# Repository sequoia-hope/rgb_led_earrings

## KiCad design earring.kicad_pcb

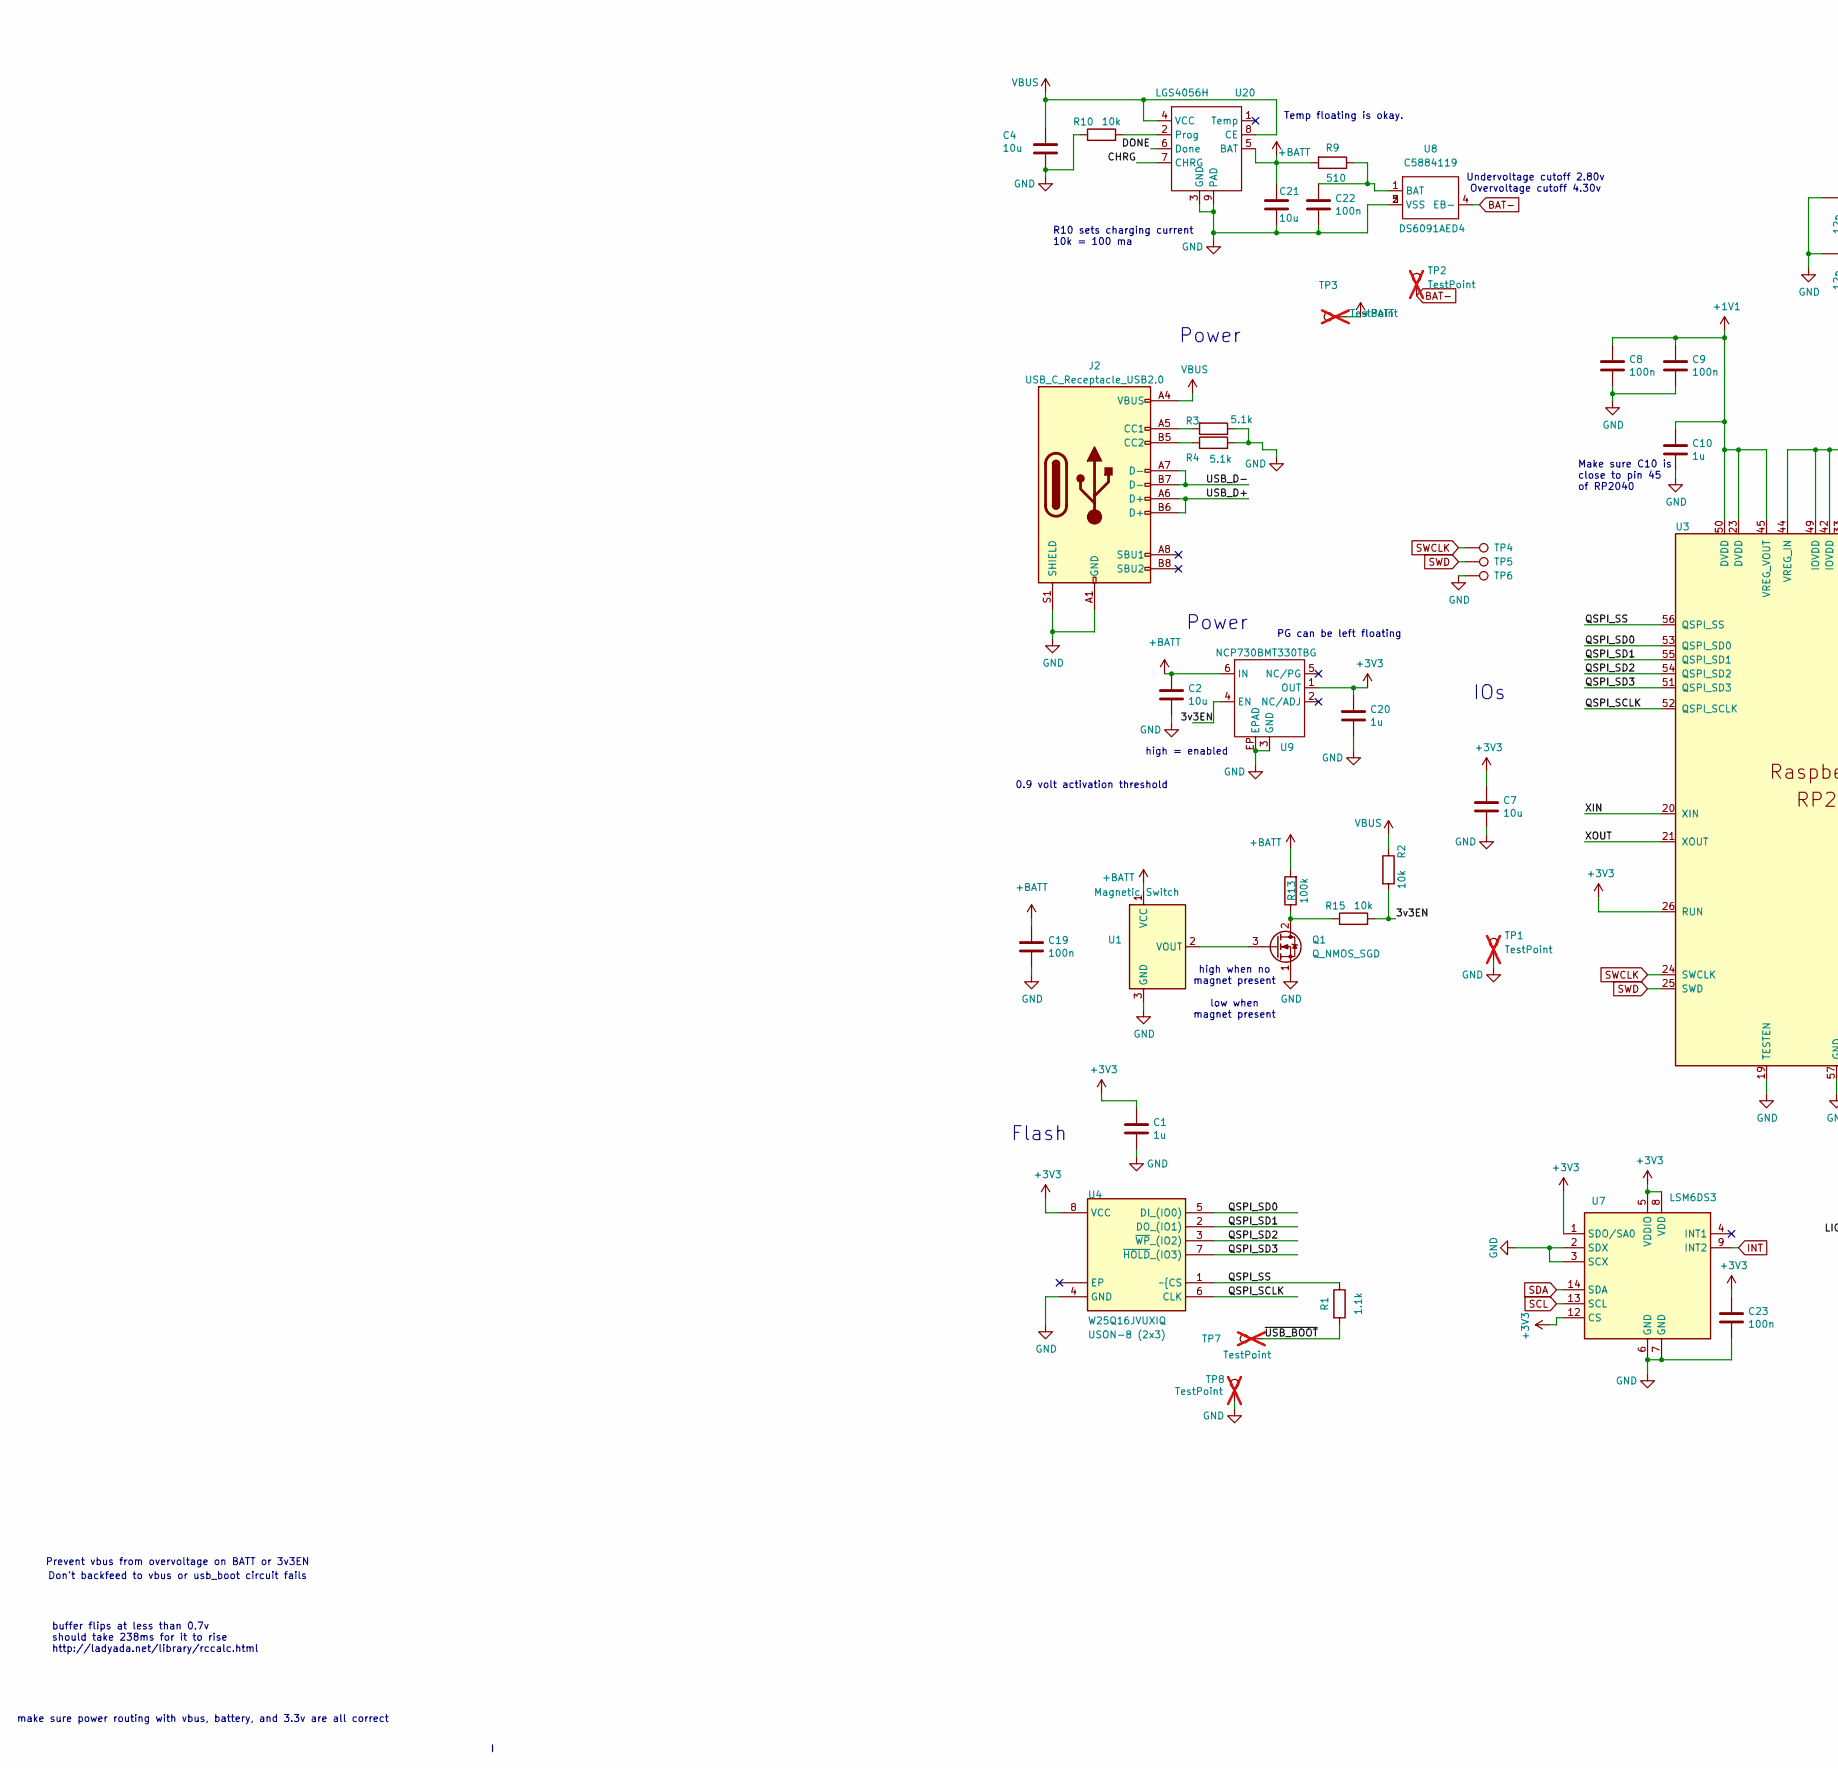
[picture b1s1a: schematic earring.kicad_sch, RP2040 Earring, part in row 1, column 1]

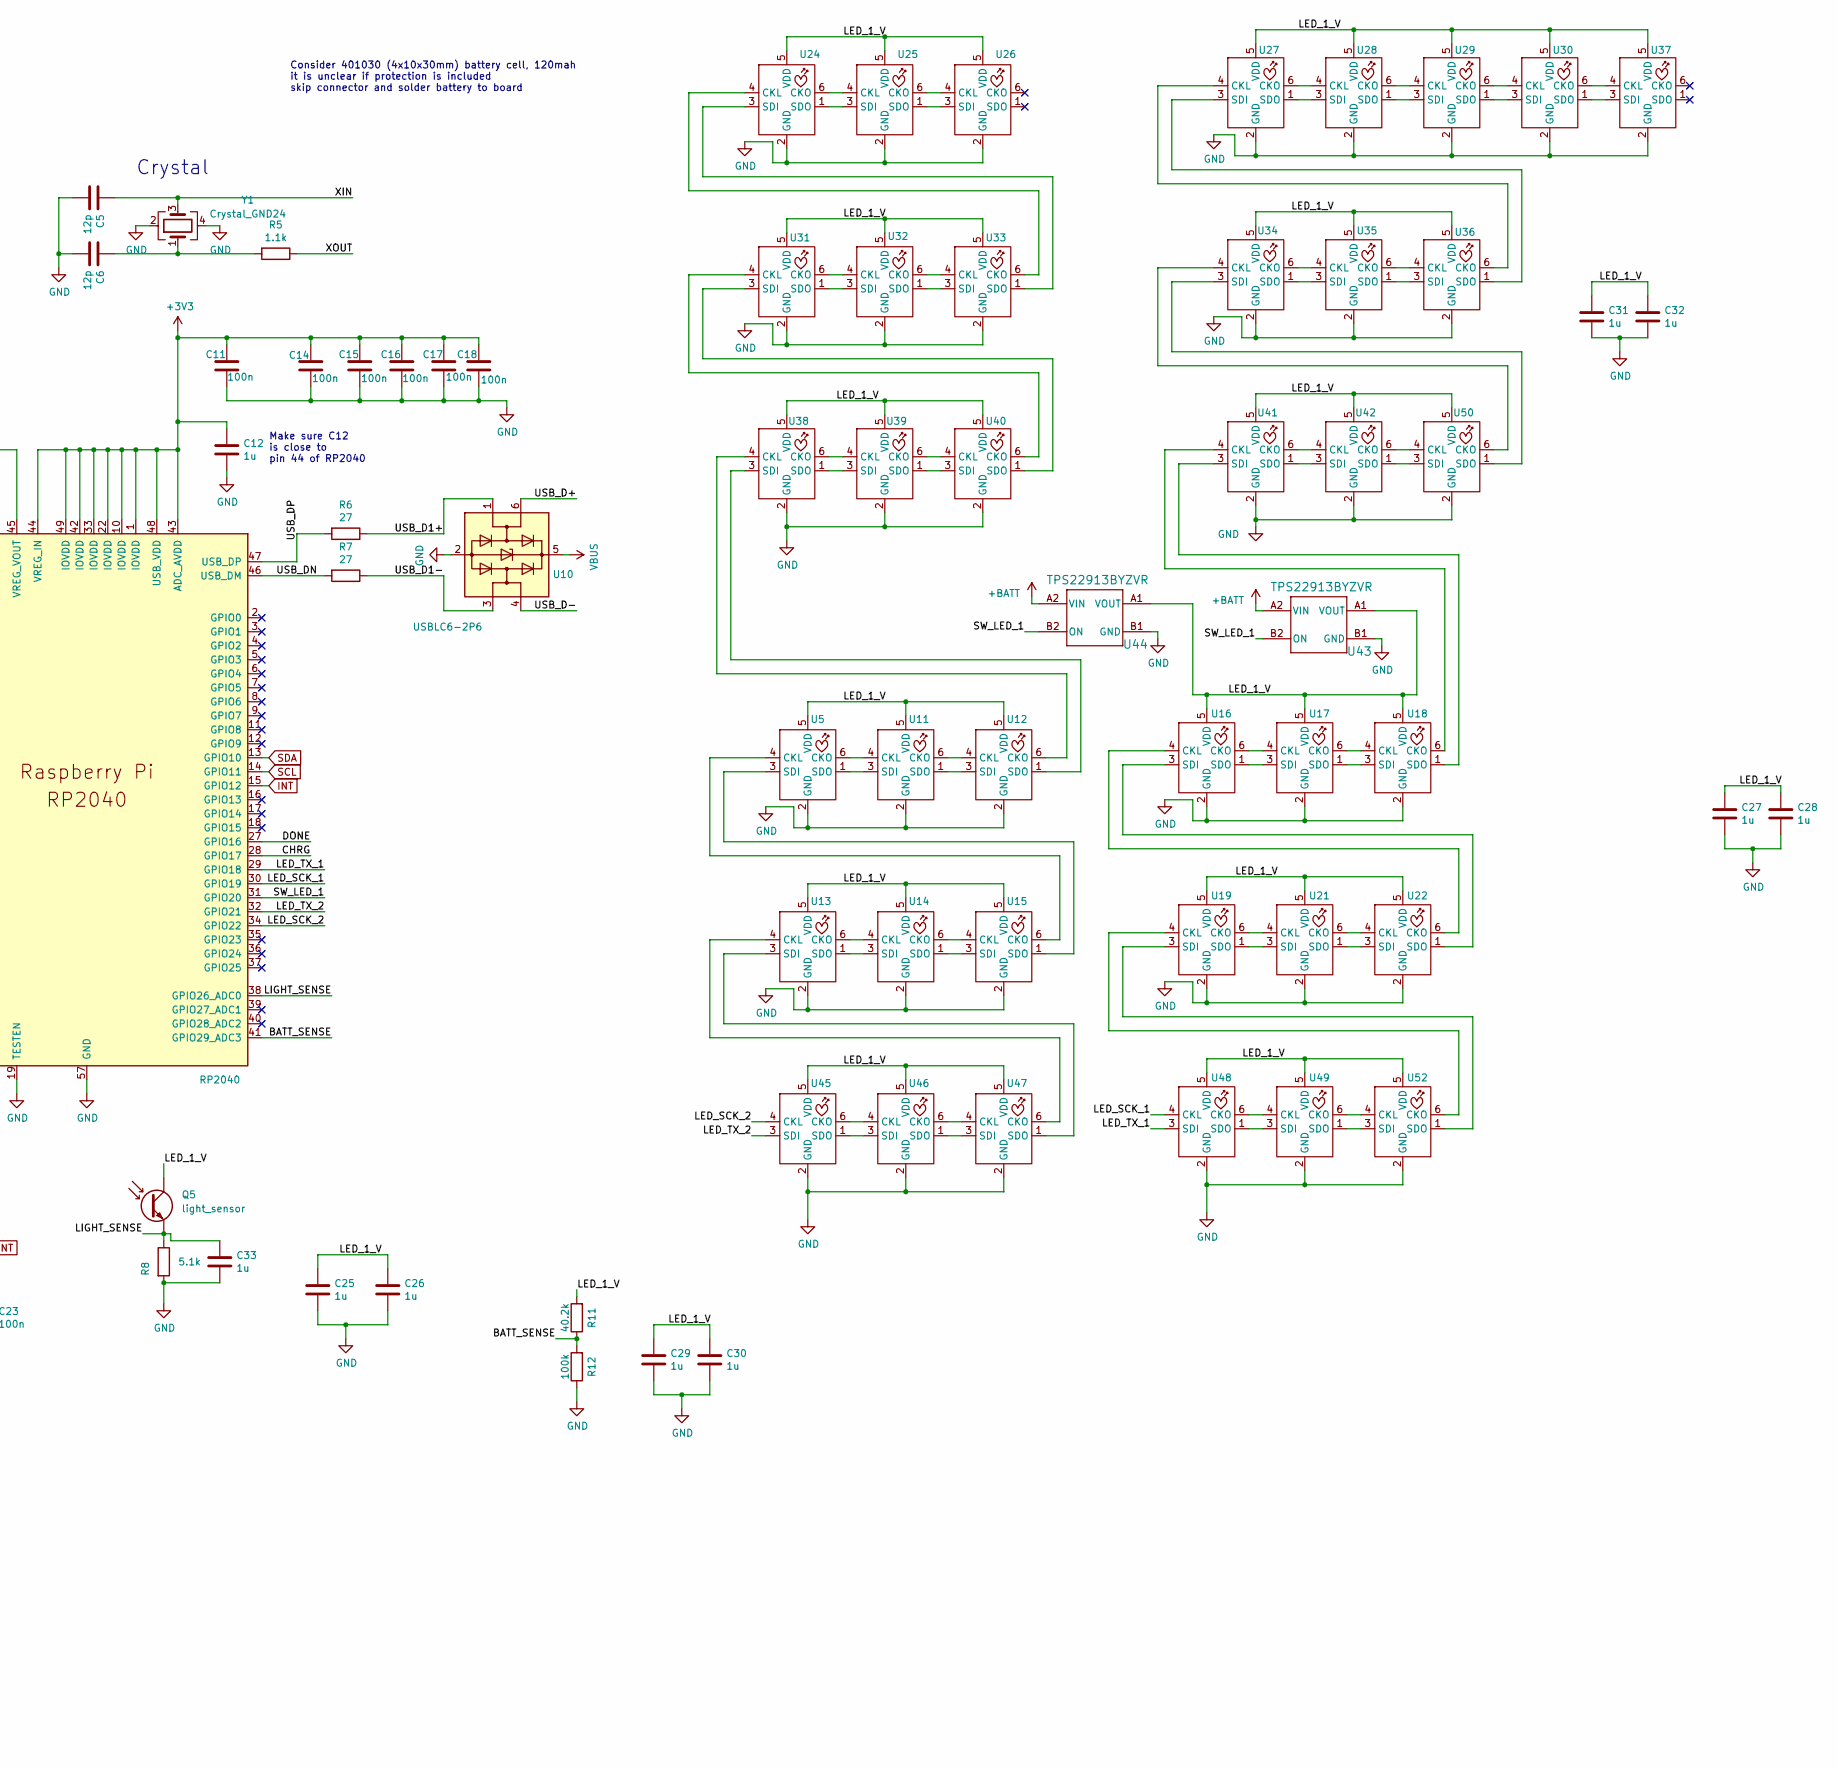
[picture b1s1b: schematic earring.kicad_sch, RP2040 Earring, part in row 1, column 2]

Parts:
C1, C10, C12, C20, C25, C26, C27, C28, C29, C30, C31, C32, C33: 1u; C_0402_1005Metric; LCSC C29266
C2, C4, C7, C21: 10u; C_0402_1005Metric; LCSC C315248
C5, C6: 12p; C_0402_1005Metric; LCSC C1547
C8, C9, C11, C14, C15, C16, C17, C18, C19, C22, C23: 100n; C_0402_1005Metric; LCSC C60474
J2: USB_C_Receptacle_USB2.0; USB-C-TH_GT-USB-7055; LCSC C2686963
Q1: Q_NMOS_SGD; DFN1006-3L_L1.0-W0.6-BL; LCSC C504101
Q5: light_sensor; LED_0603_1608Metric; LCSC C146233
R1, R5: 1.1k; R_0402_1005Metric; LCSC C325543
R2, R10, R15: 10k; R_0402_1005Metric; LCSC C60490
R3, R4, R8: 5.1k; R_0402_1005Metric; LCSC C25905
R6, R7: 27; R_0402_1005Metric; LCSC C138021
R9: 510; R_0402_1005Metric; LCSC C137860
R11: 40.2k; R_0402_1005Metric; LCSC C25893
R12, R13: 100k; R_0402_1005Metric; LCSC C60491
TP1, TP7, TP8: TestPoint; TestPoint_Pad_D1.0mm; LCSC C238130; not fitted
TP2, TP3: TestPoint; TestPoint_Pad_2.0x2.0mm; LCSC C238130; not fitted
TP4, TP5, TP6: TestPoint; TestPoint_Pad_1.0x1.0mm
U1: Magnetic Switch; DFN1608-3_L1.5-W0.8-P0.42-BL-EP; LCSC C879626
U3: RP2040; RP2040-QFN-56; LCSC C2040
U4: W25Q16JVUXIQ; IC_W25Q16JVUXIQ_TR; MPN W25Q16JVUXIQ; LCSC C2843335
U5, U11, U12, U13, U14, U15, U16, U17, U18, U19, U21, U22, U24, U25, U26, U27, U28, U29, U30, U31, U32, U33, U34, U35, U36, U37, U38, U39, U40, U41, U42, U45, U46, U47, U48, U49, U50, U52: LED-SK9822-EC20
U7: LSM6DS3; LGA-14_3x2.5mm_P0.5mm_LayoutBorder3x4y; LCSC C2829074
U8: DS6091AED4; DFN1x1; LCSC C5884119
U9: NCP730BMT330TBG; WDFN-6-2x2; LCSC C892821
U10: USBLC6-2P6; SOT-666; LCSC C2827693
U20: LGS4056H; DFN-8-1EP_2x2mm_P0.5mm_EP0.9x1.5mm; LCSC C5124109
U43, U44: TPS22913BYZVR; YZV0004ADAD; LCSC C544698
Y1: Crystal_GND24; Crystal_SMD_2520-4Pin_2.5x2.0mm; LCSC C284155

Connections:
+1V1: C8.1, C9.1, C10.1, U3.23 (DVDD), U3.45 (VREG_VOUT), U3.50 (DVDD)
+3V3: C1.1, C7.1, C11.1, C12.1, C14.1, C15.1, C16.1, C17.1, C18.1, C20.1, C23.1, U3.1 (IOVDD), U3.10 (IOVDD), U3.22 (IOVDD), U3.26 (RUN), U3.33 (IOVDD), U3.42 (IOVDD), U3.43 (ADC_AVDD), U3.44 (VREG_IN), U3.48 (USB_VDD), U3.49 (IOVDD), U4.8 (VCC), U7.1 (SDO/SA0), U7.5 (VDDIO), U7.8 (VDD), U7.12 (CS), U9.1 (OUT)
+BATT: C2.1, C19.1, C21.1, R9.2, R13.2, TP3.1, U1.1 (VCC), U9.6 (IN), U20.5 (BAT), U43.A2 (VIN), U44.A2 (VIN)
/3v3EN: R2.2, R15.2, U9.4 (EN)
/BATT_SENSE: R11.1, R12.2, U3.41 (GPIO29_ADC3)
/CHRG: U3.28 (GPIO17), U20.7 (CHRG)
/DONE: U3.27 (GPIO16), U20.6 (Done)
/LED_1_V: C25.1, C26.1, C27.1, C28.1, C29.1, C30.1, C31.1, C32.1, Q5.1, R11.2, U5.5 (VDD), U11.5 (VDD), U12.5 (VDD), U13.5 (VDD), U14.5 (VDD), U15.5 (VDD), U16.5 (VDD), U17.5 (VDD), U18.5 (VDD), U19.5 (VDD), U21.5 (VDD), U22.5 (VDD), U24.5 (VDD), U25.5 (VDD), U26.5 (VDD), U27.5 (VDD), U28.5 (VDD), U29.5 (VDD), U30.5 (VDD), U31.5 (VDD), U32.5 (VDD), U33.5 (VDD), U34.5 (VDD), U35.5 (VDD), U36.5 (VDD), U37.5 (VDD), U38.5 (VDD), U39.5 (VDD), U40.5 (VDD), U41.5 (VDD), U42.5 (VDD), U43.A1 (VOUT), U44.A1 (VOUT), U45.5 (VDD), U46.5 (VDD), U47.5 (VDD), U48.5 (VDD), U49.5 (VDD), U50.5 (VDD), U52.5 (VDD)
/LED_SCK_1: U3.30 (GPIO19), U48.4 (CKL)
/LED_SCK_2: U3.34 (GPIO22), U45.4 (CKL)
/LED_TX_1: U3.29 (GPIO18), U48.3 (SDI)
/LED_TX_2: U3.32 (GPIO21), U45.3 (SDI)
/LIGHT_SENSE: C33.1, Q5.2, R8.1, U3.38 (GPIO26_ADC0)
/QSPI_SCLK: U3.52 (QSPI_SCLK), U4.6 (CLK)
/QSPI_SD0: U3.53 (QSPI_SD0), U4.5 (DI_(IO0))
/QSPI_SD1: U3.55 (QSPI_SD1), U4.2 (DO_(IO1))
/QSPI_SD2: U3.54 (QSPI_SD2), U4.3 (~WP_(IO2))
/QSPI_SD3: U3.51 (QSPI_SD3), U4.7 (~HOLD_(IO3))
/QSPI_SS: R1.1, U3.56 (QSPI_SS), U4.1 (~{CS)
/SW_LED_1: U3.31 (GPIO20), U43.B2 (ON), U44.B2 (ON)
/USB_D1+: R6.1, U10.1 (I/O1)
/USB_D1-: R7.1, U10.3 (I/O2)
/USB_D+: J2.A6 (D+), J2.B6 (D+), U10.6 (I/O1)
/USB_D-: J2.A7 (D-), J2.B7 (D-), U10.4 (I/O2)
/USB_DN: R7.2, U3.46 (USB_DM)
/USB_DP: R6.2, U3.47 (USB_DP)
/XIN: C5.1, U3.20 (XIN), Y1.3
/XOUT: R5.1, U3.21 (XOUT)
/~USB_BOOT: R1.2, TP7.1
BAT-: TP2.1, U8.4 (EB-)
GND: C1.2, C2.2, C4.2, C5.2, C6.2, C7.2, C8.2, C9.2, C10.2, C11.2, C12.2, C14.2, C15.2, C16.2, C17.2, C18.2, C19.2, C20.2, C21.2, C22.2, C23.2, C25.2, C26.2, C27.2, C28.2, C29.2, C30.2, C31.2, C32.2, C33.2, J2.A1 (GND), J2.A12 (GND), J2.B1 (GND), J2.B12 (GND), J2.S1 (SHIELD), Q1.1 (S), R3.1, R4.2, R8.2, R10.1, R12.1, TP1.1, TP6.1, TP8.1, U1.3 (GND), U3.19 (TESTEN), U3.57 (GND), U4.4 (GND), U5.2 (GND), U7.2 (SDX), U7.3 (SCX), U7.6 (GND), U7.7 (GND), U8.2 (VSS), U8.3 (VSS), U8.5 (VSS), U9.3 (GND), U9.EP (EPAD), U10.2 (GND), U11.2 (GND), U12.2 (GND), U13.2 (GND), U14.2 (GND), U15.2 (GND), U16.2 (GND), U17.2 (GND), U18.2 (GND), U19.2 (GND), U20.3 (GND), U20.9 (PAD), U21.2 (GND), U22.2 (GND), U24.2 (GND), U25.2 (GND), U26.2 (GND), U27.2 (GND), U28.2 (GND), U29.2 (GND), U30.2 (GND), U31.2 (GND), U32.2 (GND), U33.2 (GND), U34.2 (GND), U35.2 (GND), U36.2 (GND), U37.2 (GND), U38.2 (GND), U39.2 (GND), U40.2 (GND), U41.2 (GND), U42.2 (GND), U43.B1 (GND), U44.B1 (GND), U45.2 (GND), U46.2 (GND), U47.2 (GND), U48.2 (GND), U49.2 (GND), U50.2 (GND), U52.2 (GND), Y1.2, Y1.4
INT: U3.15 (GPIO12), U7.9 (INT2)
unnamed: C6.1, R5.2, Y1.1
unnamed: J2.A5 (CC1), R3.2
unnamed: J2.B5 (CC2), R4.1
unnamed: Q1.2 (D), R13.1, R15.1
unnamed: Q1.3 (G), U1.2 (VOUT)
unnamed: C22.1, R9.1, U8.1 (BAT)
unnamed: U5.6 (CKO), U11.4 (CKL)
unnamed: U11.6 (CKO), U12.4 (CKL)
unnamed: U5.1 (SDO), U11.3 (SDI)
unnamed: U11.1 (SDO), U12.3 (SDI)
unnamed: U12.6 (CKO), U38.4 (CKL)
unnamed: U12.1 (SDO), U38.3 (SDI)
unnamed: U13.4 (CKL), U47.6 (CKO)
unnamed: U13.6 (CKO), U14.4 (CKL)
unnamed: U13.3 (SDI), U47.1 (SDO)
unnamed: U13.1 (SDO), U14.3 (SDI)
unnamed: U14.6 (CKO), U15.4 (CKL)
unnamed: U14.1 (SDO), U15.3 (SDI)
unnamed: U5.4 (CKL), U15.6 (CKO)
unnamed: U5.3 (SDI), U15.1 (SDO)
unnamed: U16.4 (CKL), U22.6 (CKO)
unnamed: U16.6 (CKO), U17.4 (CKL)
unnamed: U16.3 (SDI), U22.1 (SDO)
unnamed: U16.1 (SDO), U17.3 (SDI)
unnamed: U17.6 (CKO), U18.4 (CKL)
unnamed: U17.1 (SDO), U18.3 (SDI)
unnamed: U18.6 (CKO), U41.4 (CKL)
unnamed: U18.1 (SDO), U41.3 (SDI)
unnamed: U19.4 (CKL), U52.6 (CKO)
unnamed: U19.6 (CKO), U21.4 (CKL)
unnamed: U19.3 (SDI), U52.1 (SDO)
unnamed: U19.1 (SDO), U21.3 (SDI)
unnamed: R10.2, U20.2 (Prog)
unnamed: U21.6 (CKO), U22.4 (CKL)
unnamed: U21.1 (SDO), U22.3 (SDI)
unnamed: U24.4 (CKL), U33.6 (CKO)
unnamed: U24.6 (CKO), U25.4 (CKL)
unnamed: U24.3 (SDI), U33.1 (SDO)
unnamed: U24.1 (SDO), U25.3 (SDI)
unnamed: U25.6 (CKO), U26.4 (CKL)
unnamed: U25.1 (SDO), U26.3 (SDI)
unnamed: U27.4 (CKL), U36.6 (CKO)
unnamed: U27.6 (CKO), U28.4 (CKL)
unnamed: U27.3 (SDI), U36.1 (SDO)
unnamed: U27.1 (SDO), U28.3 (SDI)
unnamed: U28.6 (CKO), U29.4 (CKL)
unnamed: U28.1 (SDO), U29.3 (SDI)
unnamed: U29.6 (CKO), U30.4 (CKL)
unnamed: U29.1 (SDO), U30.3 (SDI)
unnamed: U30.6 (CKO), U37.4 (CKL)
unnamed: U30.1 (SDO), U37.3 (SDI)
unnamed: U31.4 (CKL), U40.6 (CKO)
unnamed: U31.6 (CKO), U32.4 (CKL)
unnamed: U31.3 (SDI), U40.1 (SDO)
unnamed: U31.1 (SDO), U32.3 (SDI)
unnamed: U32.6 (CKO), U33.4 (CKL)
unnamed: U32.1 (SDO), U33.3 (SDI)
unnamed: U34.4 (CKL), U50.6 (CKO)
unnamed: U34.6 (CKO), U35.4 (CKL)
unnamed: U34.3 (SDI), U50.1 (SDO)
unnamed: U34.1 (SDO), U35.3 (SDI)
unnamed: U35.6 (CKO), U36.4 (CKL)
unnamed: U35.1 (SDO), U36.3 (SDI)
unnamed: U38.6 (CKO), U39.4 (CKL)
unnamed: U38.1 (SDO), U39.3 (SDI)
unnamed: U39.6 (CKO), U40.4 (CKL)
unnamed: U39.1 (SDO), U40.3 (SDI)
unnamed: U41.6 (CKO), U42.4 (CKL)
unnamed: U41.1 (SDO), U42.3 (SDI)
unnamed: U42.6 (CKO), U50.4 (CKL)
unnamed: U42.1 (SDO), U50.3 (SDI)
unnamed: U45.6 (CKO), U46.4 (CKL)
unnamed: U45.1 (SDO), U46.3 (SDI)
unnamed: U46.6 (CKO), U47.4 (CKL)
unnamed: U46.1 (SDO), U47.3 (SDI)
unnamed: U48.6 (CKO), U49.4 (CKL)
unnamed: U48.1 (SDO), U49.3 (SDI)
unnamed: U49.6 (CKO), U52.4 (CKL)
unnamed: U49.1 (SDO), U52.3 (SDI)
SCL: U3.14 (GPIO11), U7.13 (SCL)
SDA: U3.13 (GPIO10), U7.14 (SDA)
SWCLK: TP4.1, U3.24 (SWCLK)
SWD: TP5.1, U3.25 (SWD)
VBUS: C4.1, J2.A4 (VBUS), J2.A9 (VBUS), J2.B4 (VBUS), J2.B9 (VBUS), R2.1, U10.5 (VBUS), U20.4 (VCC), U20.8 (CE)

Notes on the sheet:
Make sure C10 is close to pin 45 of RP2040
Prevent vbus from overvoltage on BATT or 3v3EN
Consider 401030 (4x10x30mm) battery cell, 120mah it is unclear if protection is included skip connector and solder battery to board
Power
Crystal
R10 sets charging current 10k = 100 ma
IOs
Undervoltage cutoff 2.80v Overvoltage cutoff 4.30v
high when no magnet present low when magnet present
Don't backfeed to vbus or usb_boot circuit fails
PG can be left floating
Make sure C12 is close to pin 44 of RP2040
0.9 volt activation threshold
make sure power routing with vbus, battery, and 3.3v are all correct
high = enabled
buffer flips at less than 0.7v should take 238ms for it to rise http://ladyada.net/library/rccalc.html
Temp floating is okay.
Flash

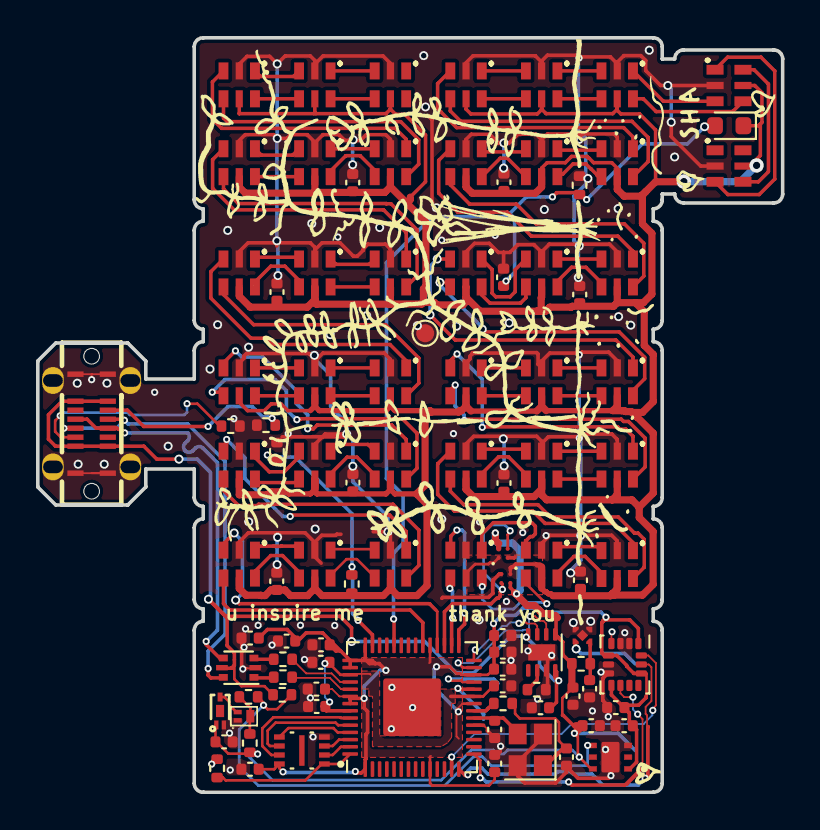
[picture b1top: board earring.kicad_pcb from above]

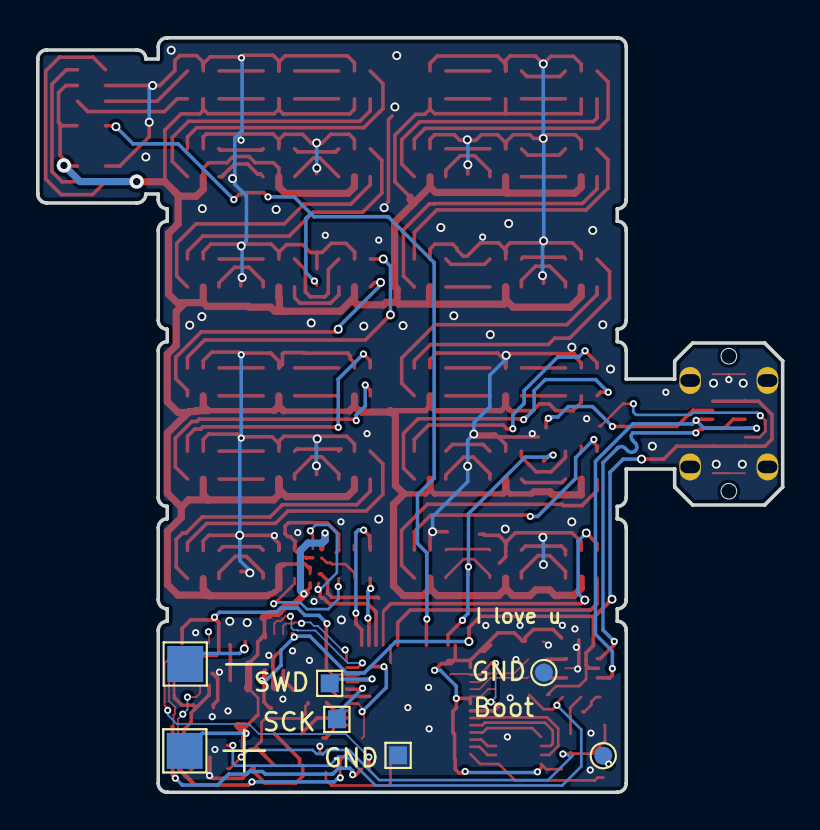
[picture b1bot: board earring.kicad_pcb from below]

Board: 2 copper layers, 41.4 x 41.9 mm, 104 parts (7 on the bottom side), 116 nets.

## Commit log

2025-03-09 rework power control to simplify and remove VBAT from MCU pins
2025-05-18 check in complex startup circuit before simplification
2025-05-18 simplify power and boot circuit
2025-06-13 pcb files seem possibly ready to order
2025-06-20 about to rewire
2025-06-25 Fixed power circuit and ordered June 2025
2025-07-02 Had to cancel order, fixing DRC issues in progress.
2025-07-15 more clean up. looking pretty good
2025-07-21 updated with better clearance, ordered this rev after canceling the last order

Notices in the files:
earring.kicad_sch:
LICENSE: CERN-OHL-P
